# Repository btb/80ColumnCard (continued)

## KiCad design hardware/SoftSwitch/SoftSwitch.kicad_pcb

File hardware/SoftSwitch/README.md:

# SoftSwitch

A clone of the [Videx Soft Video Switch](../../documents/videx_soft_video_switch_manual.pdf)

[Interactive BOM](https://btb.github.io/80ColumnCard/hardware/SoftSwitch/bom/)

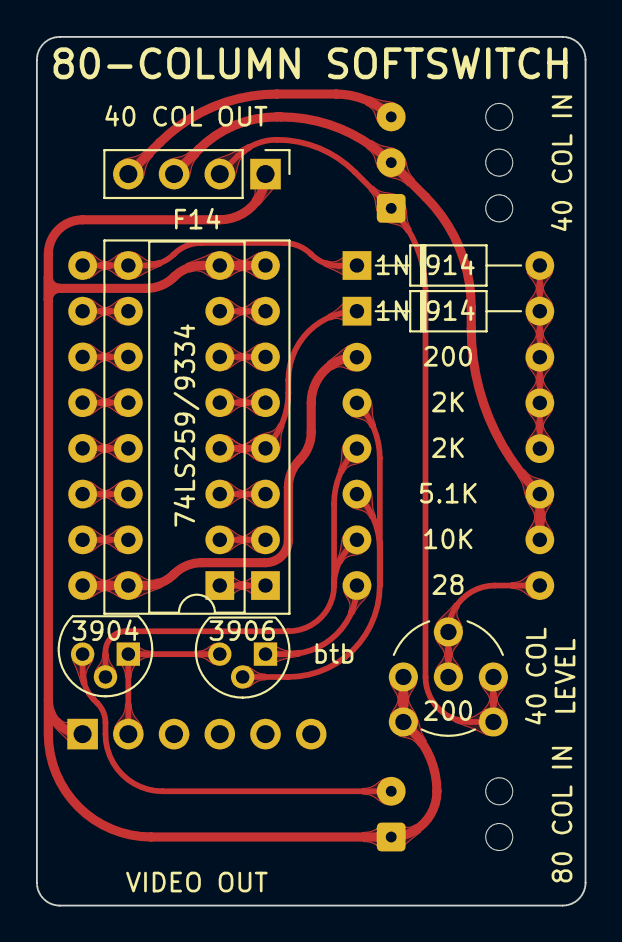
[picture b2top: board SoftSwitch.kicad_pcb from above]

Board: 2 copper layers, 30.5 x 48.3 mm, 17 parts (0 on the bottom side), 26 nets.

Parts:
D1, D2: 1N 914; D_DO-35_SOD27_P10.16mm_Horizontal
F14: 74LS259/9334; DIP-16_W7.62mm_Socket
FP14: F14 passthrough; DIP-16_W7.62mm_Socket
J1: 80 COL IN; SolderWire-0.1sqmm_1x02_P3.6mm_D0.4mm_OD1mm_Relief
J2: 40 COL IN; SolderWire-0.1sqmm_1x03_P3.6mm_D0.4mm_OD1mm_Relief
J3: VIDEO OUT; PinHeader_1x06_P2.54mm_Horizontal
J4: 40 COL OUT; PinHeader_1x04_P2.54mm_Vertical
Q1: 3904; TO-92
Q2: 3906; TO-92
R1: 200; R_Axial_DIN0207_L6.3mm_D2.5mm_P10.16mm_Horizontal
R2, R3: 2K; R_Axial_DIN0207_L6.3mm_D2.5mm_P10.16mm_Horizontal
R4: 10K; R_Axial_DIN0207_L6.3mm_D2.5mm_P10.16mm_Horizontal
R5: 5.1K; R_Axial_DIN0207_L6.3mm_D2.5mm_P10.16mm_Horizontal
R6: 28; R_Axial_DIN0207_L6.3mm_D2.5mm_P10.16mm_Horizontal
RV1: 200; Multi_Potentiometer_6mm_Vertical

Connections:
+5V: F14.16 (VCC), FP14.16 (VCC), R1.2
/+12V: J2.3 (+12), J4.4
/-5V: J2.2 (-5), J4.3, R4.2, R5.1
/SWITCHED VIDEO OUT: J3.2, Q1.1 (E), Q2.3 (C)
GND: F14.8 (GND), FP14.8 (GND), J1.1, J3.1, J4.1, RV1.3
unnamed: D1.1 (K), F14.4 (Q0), FP14.4 (Q0)
unnamed: D1.2 (A), D2.2 (A), R1.1, R2.1, R3.1
unnamed: D2.1 (K), F14.9 (Q4), FP14.9 (Q4)
unnamed: F14.1 (A0), FP14.1 (A0)
unnamed: F14.2 (A1), FP14.2 (A1)
unnamed: F14.3 (A2), FP14.3 (A2)
unnamed: F14.5 (Q1), FP14.5 (Q1)
unnamed: F14.6 (Q2), FP14.6 (Q2)
unnamed: F14.7 (Q3), FP14.7 (Q3)
unnamed: F14.10 (Q5), FP14.10 (Q5)
unnamed: F14.11 (Q6), FP14.11 (Q6)
unnamed: F14.12 (Q7), FP14.12 (Q7)
unnamed: F14.13 (D), FP14.13 (D)
unnamed: F14.14 (E), FP14.14 (E)
unnamed: F14.15 (Clr), FP14.15 (Clr)
unnamed: J1.2, Q1.3 (C)
unnamed: J2.1 (IN), J4.2, RV1.1
unnamed: Q1.2 (B), R2.2, R4.1
unnamed: Q2.1 (E), R6.2
unnamed: Q2.2 (B), R3.2, R5.2
unnamed: R6.1, RV1.2

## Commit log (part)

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2022-09-19 add files
2022-09-19 allow bigger RAM and ROM chips
2022-09-19 make traces for multiplexor high bit easier to cut
2022-09-20 update render and BOM
2022-09-20 tweak
2022-09-21 rename alternate char rom footprints
2022-09-23 move board to "hardware" subdir
2022-09-23 Add Videx firmware and disassembly
2022-09-23 add redirect
2022-09-23 DEV->DEVICE_SELECT
2022-09-23 add datasheets
2022-09-23 Document initialization of CRTC registers
2022-09-25 add clone firmware
2022-09-25 keep videx copyright on the clone fw
2022-09-25 minor edits
2022-09-25 connect CRTC A11 to SRAM multiplexer. add jumpers for selectable firmware
2022-09-25 better datasheet
2022-09-26 clean up, add jumpers for fw/char selection
2022-09-27 more cleanups
2022-09-27 add some annotations
2022-09-29 use more common component sizes
2022-09-29 Add Character ROMS from Apple II Documentation Project
2022-09-29 add "Videx Videoterm Character ROM Graphics.bin"
2022-10-07 better character roms
2022-10-07 Add SoftSwitch
2022-10-08 make softswitch narrower, general improvements
2022-10-08 fab doc for C1,C4
2022-10-08 add gerbers
2022-10-08 add revision
2022-10-09 fiddling
2022-10-09 use rev 0 image
2023-04-14 keep bytes in disassembly
2023-05-21 fix merge error
2023-05-21 add SoftSwitch gerbers
2023-05-21 add softswitch readme
2023-05-21 add soft switch manual
2023-05-23 revert fiddling
2023-06-27 Add cc65-compatible source file and Makefile.
2023-06-27 Add construction notes for the card.
2023-06-27 Update README.md
    merge in text from wiki
2023-06-27 Update README.md
    fixes
2023-06-28 Use underscore instead of spaces
    Make really doesn't work with spaces in filenames.
2023-09-16 Kicad 7, miscellaneous tweaks
